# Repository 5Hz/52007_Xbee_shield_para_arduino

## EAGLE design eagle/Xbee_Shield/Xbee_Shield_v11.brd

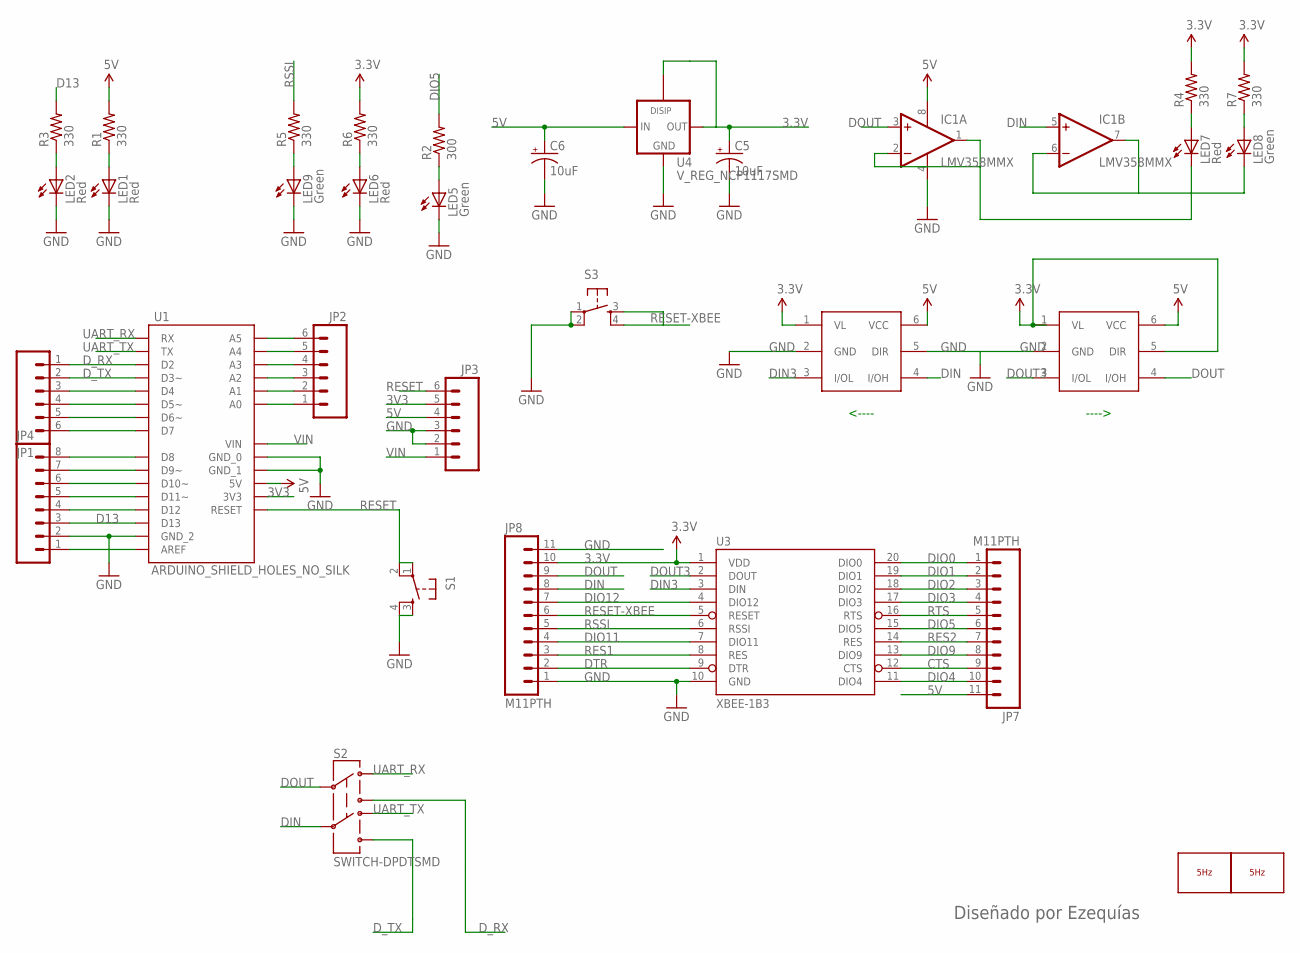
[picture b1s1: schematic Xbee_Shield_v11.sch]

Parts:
C5, C6: 10uF; EIA3216
IC1: LMV358MMX; MSOP08
JP1, JP2, JP3: M06SIP; 1X06
JP4: M081X08; 1X08
JP7, JP8: M11PTH; 1X11
LED1, LED2, LED6, LED7: Red; LED-0603
LED5, LED8, LED9: Green; LED-0603
LOGO1: LOGO_5HZ_H_20MM; 5HZ_LOGO_H_20MM
LOGO2: LOGO_5HZ_WEB_COOPER_10MM; 5HZ_WEB_COOPER_10MM
R1, R3, R4, R5, R6, R7: 330; 0603-RES
R2: 300; 0603-RES
S1, S3: TAC_SWITCHSMD; TACTILE_SWITCH_SMD
S2: SWITCH-DPDTSMD; AYZ0202
U1: ARDUINO_SHIELD_HOLES_NO_SILK; UNO_SHIELD_HOLES_NO_SILK
U3: XBEE-1B3; XBEE-SMD
U4: V_REG_NCP1117SMD; SOT223
U$7, U$8: MAX337; SOT-363

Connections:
3.3V: C5.A (+), JP8.10, R4.2, R6.2, R7.2, U3.1 (VDD), U4.2 (OUT), U4.4, U$7.1 (VL), U$8.1 (VL), U$8.5 (DIR)
3V3: JP3.5, U1.3.3V (3V3)
5V: C6.A (+), IC1.8 (V+), JP3.4, JP7.11, R1.2, U1.5V, U4.3 (IN), U$7.6 (VCC), U$8.6 (VCC)
CTS: JP7.9, U3.12 (CTS)
D13: JP4.3, R3.2, U1.D13
DIN: IC1.5 (+IN), JP8.8, S2.5, U$7.4 (I/OH)
DIN3: U3.3 (DIN), U$7.3 (I/OL)
DIO0: JP7.1, U3.20 (DIO0)
DIO1: JP7.2, U3.19 (DIO1)
DIO2: JP7.3, U3.18 (DIO2)
DIO3: JP7.4, U3.17 (DIO3)
DIO4: JP7.10, U3.11 (DIO4)
DIO5: JP7.6, R2.2, U3.15 (DIO5)
DIO9: JP7.8, U3.13 (DIO9)
DIO11: JP8.4, U3.7 (DIO11)
DIO12: JP8.7, U3.4 (DIO12)
DOUT: IC1.3 (+IN), JP8.9, S2.2, U$8.4 (I/OH)
DOUT3: U3.2 (DOUT), U$8.3 (I/OL)
DTR: JP8.2, U3.9 (DTR)
D_RX: JP1.1, S2.3, U1.D2
D_TX: JP1.2, S2.6, U1.D3 (D3~)
GND: C5.C (-), C6.C (-), IC1.4 (V-), JP3.2, JP3.3, JP4.2, JP8.1, JP8.11, LED1.C, LED2.C, LED5.C, LED6.C, LED9.C, S1.3, S1.4, S3.1, S3.2, U1.GND_0, U1.GND_1, U1.GND_2, U3.10 (GND), U4.1 (GND), U$7.2 (GND), U$7.5 (DIR), U$8.2 (GND)
unnamed: JP2.6, U1.A5
unnamed: JP2.5, U1.A4
unnamed: JP2.4, U1.A3
unnamed: JP2.3, U1.A2
unnamed: JP2.2, U1.A1
unnamed: JP4.8, U1.D8
unnamed: JP4.7, U1.D9 (D9~)
unnamed: JP4.6, U1.D10 (D10~)
unnamed: JP4.5, U1.D11 (D11~)
unnamed: JP4.4, U1.D12
unnamed: IC1.1 (OUT), IC1.2 (-IN), LED7.C
unnamed: JP1.6, U1.D7
unnamed: JP1.5, U1.D6 (D6~)
unnamed: JP1.4, U1.D5 (D5~)
unnamed: JP1.3, U1.D4
unnamed: JP2.1, U1.A0
unnamed: LED1.A, R1.1
unnamed: LED6.A, R6.1
unnamed: LED7.A, R4.1
unnamed: LED8.A, R7.1
unnamed: LED9.A, R5.1
unnamed: JP4.1, U1.AREF
unnamed: IC1.6 (-IN), IC1.7 (OUT), LED8.C
unnamed: LED2.A, R3.1
unnamed: LED5.A, R2.1
RES1: JP8.3, U3.8 (RES)
RES2: JP7.7, U3.14 (RES)
RESET: JP3.6, S1.1, S1.2, U1.RES (RESET)
RESET-XBEE: JP8.6, S3.3, S3.4, U3.5 (RESET)
RSSI: JP8.5, R5.2, U3.6 (RSSI)
RTS: JP7.5, U3.16 (RTS)
UART_RX: S2.1, U1.RX
UART_TX: S2.4, U1.TX
VIN: JP3.1, U1.VIN

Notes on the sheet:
<----
---->
Diseñado por Ezequías

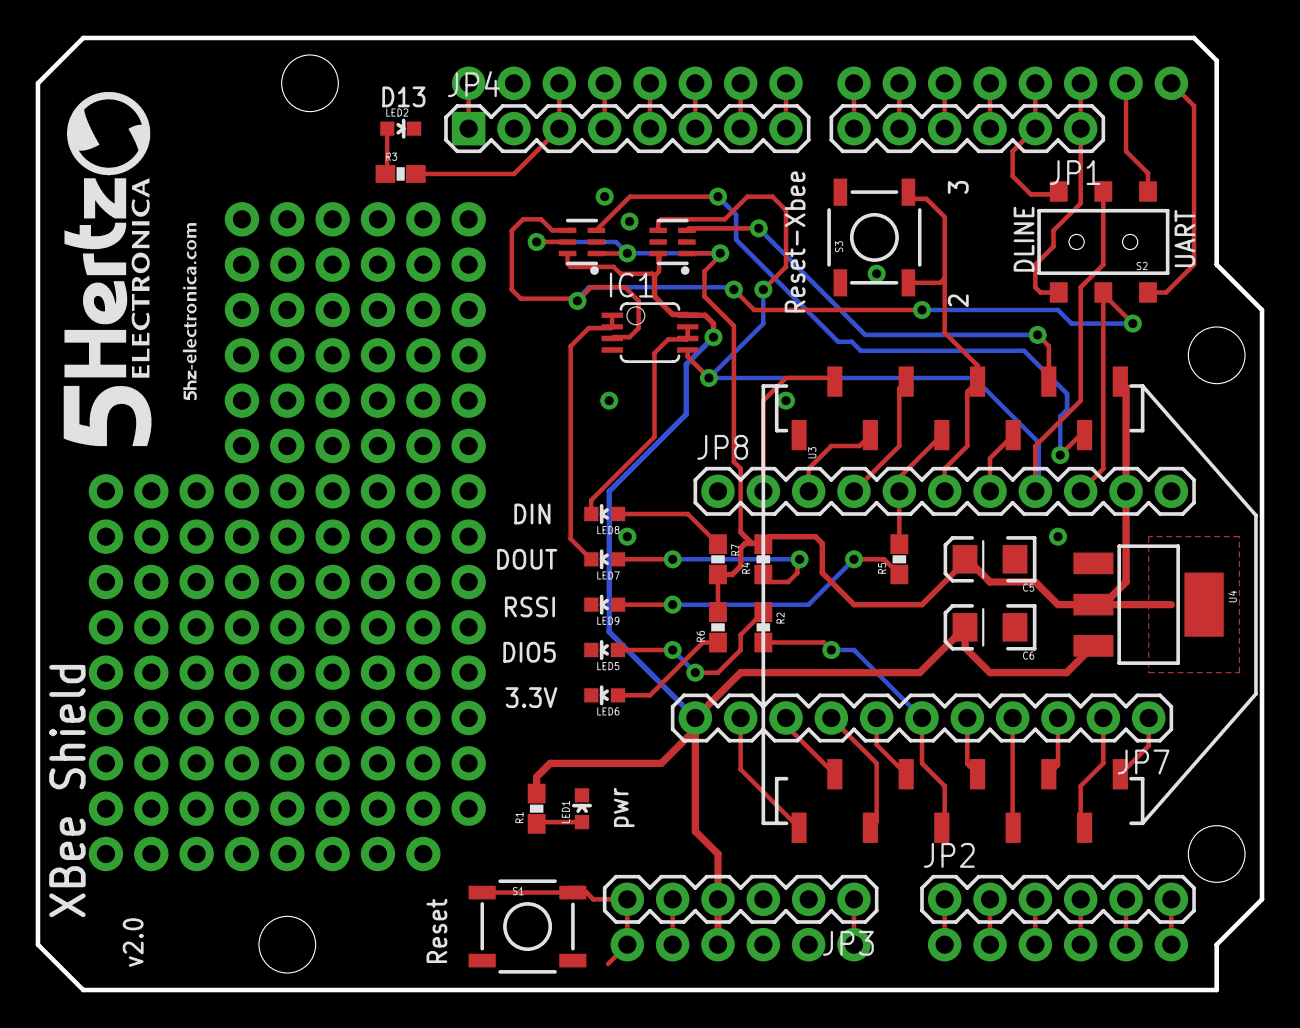
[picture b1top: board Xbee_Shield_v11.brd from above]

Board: 2 copper layers, 68.6 x 53.3 mm, 33 parts (0 on the bottom side), 56 nets.

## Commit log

2014-01-14 creación
